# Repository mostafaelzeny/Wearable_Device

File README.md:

# AD5941 Impedance Sweep Logger 🚀

Welcome to the AD5940/AD5941 Impedance Logger project! This repository allows you to perform highly accurate impedance sweeps using an ESP32 and save the resulting data automatically to CSV files on your computer.

> [!IMPORTANT]
> The Arduino IDE's Serial Monitor cannot save files! To actually save your sweeps as CSV files, you **must** use the provided python script or shell script.

## 🛠️ How to Use

Follow these steps to run sweeps and save your data:

### 1. Upload to ESP32
Open `AD5940_Impedance.ino` in the Arduino IDE. Compile and upload the sketch to your ESP32. 
**Make sure you close the Serial Monitor in the Arduino IDE after uploading!**

### 2. Run the Logger
Open your terminal in this folder and run the provided helper script:
```bash
./save_readings.sh
```
*(Alternatively, you can run `python3 save_readings.py` directly).*

### 3. Let it Sweep!
The script will automatically connect to your board and begin saving the impedance sweeps sequentially into separate CSV files (`sweep_1.csv`, `sweep_2.csv`, `sweep_3.csv`).

> [!TIP]
> After all sweeps complete, the script will pause. Press **Enter** in your terminal to restart another round of sweeps without having to physically reset the board!

---

## ⚙️ Adjusting the Configuration

All sweep configurations are located at the very top of the `AD5940_Impedance.ino` file under **USER CONFIGURABLE PARAMETERS**. Here is a breakdown of the things you can easily change to fit your needs:

### Sweep Parameters
| Parameter | Default | Description |
|---|---|---|
| `NUM_SWEEPS` | `3` | How many full frequency sweeps to execute before pausing. |
| `SWEEP_START_FREQ` | `100.0f` | The starting frequency in Hz. |
| `SWEEP_STOP_FREQ` | `100e3f` | The stopping frequency in Hz (e.g., 100,000 Hz or 100kHz). |
| `SWEEP_POINTS` | `101` | The number of measurement data points taken per sweep. |
| `SWEEP_LOG` | `bTRUE` | Set to `bTRUE` for logarithmic frequency spacing, or `bFALSE` for linear. |

### Analog Front-End (AFE) Parameters
| Parameter | Default | Description |
|---|---|---|
| `RTIA_RESISTOR` | `HSTIARTIA_5K` | High-Speed TIA Gain. Keep this lower than your lowest expected impedance to avoid clipping. |
| `DAC_VOLT_PP` | `200.0f` | AC excitation voltage in mVpp. For biological materials, keep under 200mV. |
| `RCAL_VALUE` | `10000.0f` | Calibration resistor on the board. Make sure this matches your physical hardware (Default is 10kΩ). |

> [!CAUTION]
> If your `RTIA_RESISTOR` is too high compared to the load, the AFE will saturate and output distorted/incorrect impedance values.

---

## 🔌 Hardware Port Details

*This project is based on a port of the official AD5940 library to ESP32. It supports SPI communications at 8MHz.*

**Connections:**
The electrode switch configuration supports a **4-wire** (Kelvin) setup for high accuracy measurements. The default mapping in the code is:
- **CE0**: Drive (Force +)
- **AIN1**: Positive Sense (Sense +)
- **AIN2**: Negative Sense (Sense -)
- **AIN3**: Current Return (Force -)

*(If you are using a different 4-wire pinout, you can easily change the `SWITCH_` macros under the USER CONFIGURABLE PARAMETERS section of `AD5940_Impedance.ino`)*

*Disclaimer: This library is not officially endorsed by Analog Devices.*

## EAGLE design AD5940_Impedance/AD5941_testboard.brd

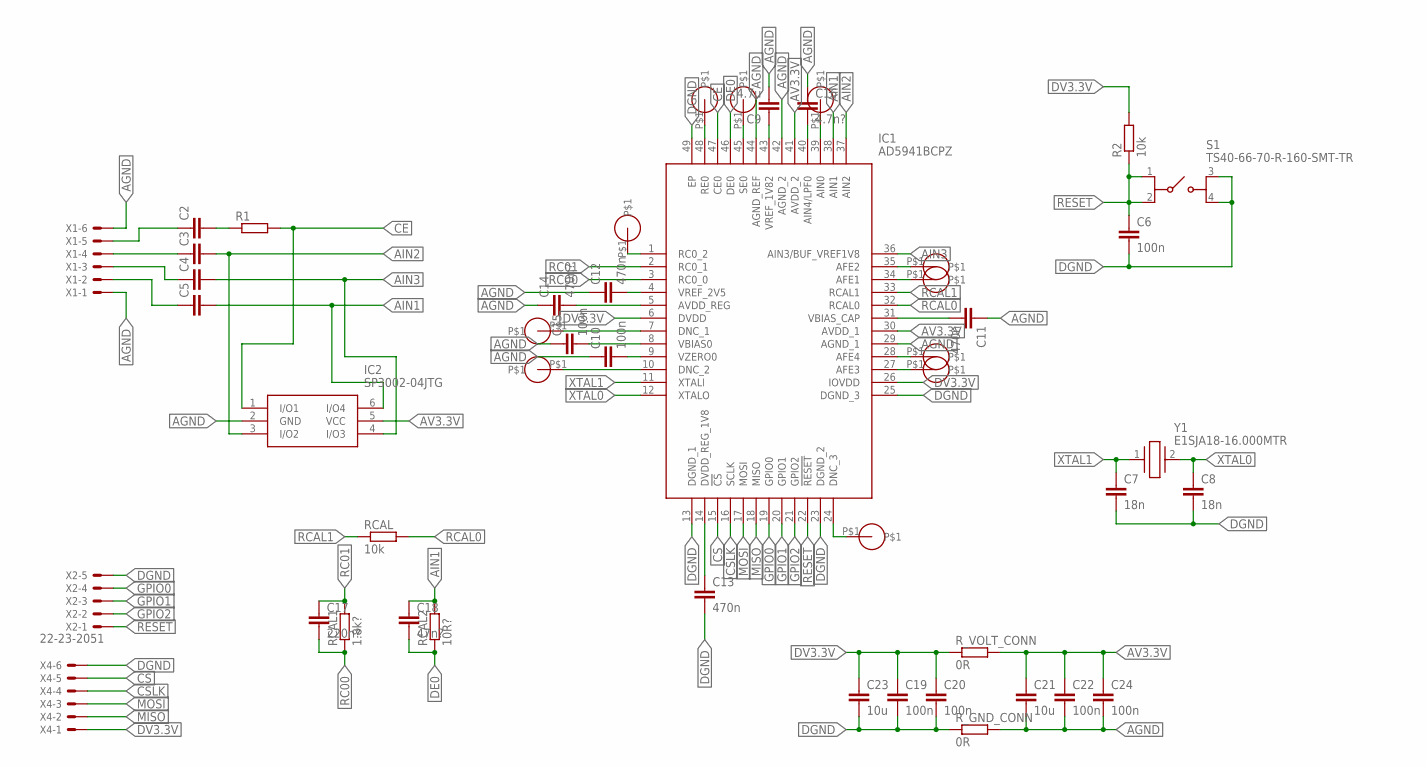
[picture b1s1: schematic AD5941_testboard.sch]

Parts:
C2, C3, C4, C5: C-EUC0805; C0805
C6, C10, C15, C19, C20, C22, C24: 100n; C0805
C7, C8: 18n; C0805
C9: 4.7u; C0805
C11, C12, C13: 470n; C0805
C14: 470n?; C0805
C16: 4.7n?; C0805
C17: 220n?; C0805
C18: 47n?; C0805
C21, C23: 10u; C0805
IC1: AD5941BCPZ; QFN50P700X700X80-49N
IC2: SP3002-04JTG; SOT65P220X110-6N
R1: R-EU_R0603; R0603
R2: 10k; R0603
RCAL: 10k; R0603
RCAL1: 1.8k?; R0603
RCAL2: 10R?; R0603
R_GND_CONN: 0R; R0603
R_VOLT_CONN: 0R; R0603
S1: TS40-66-70-R-160-SMT-TR; TS406670R160SMTTR
U$1, U$2, U$3, U$4, U$5, U$6, U$7, U$8, U$9, U$10, U$11: 1XPIN+HOLE
X1, X4: 22-23-2061
X2: 22-23-2051
Y1: E1SJA18-16.000MTR; E1SJA1816000MTR

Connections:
AGND: C9.2, C10.1, C11.1, C12.1, C14.1, C15.1, C16.1, C21.2, C22.2, C24.2, IC1.29 (AGND_1), IC1.42 (AGND_2), IC1.44 (AGND_REF), IC2.2 (GND), R_GND_CONN.2, X1.1, X1.6
AIN1: C5.2, C18.1, IC1.38 (AIN1), IC2.6 (I/O4), RCAL2.2
AIN2: C3.2, IC1.37 (AIN2), IC2.3 (I/O2)
AIN3: C4.2, IC1.36 (AIN3/BUF_VREF1V8), IC2.4 (I/O3)
AV3.3V: C21.1, C22.1, C24.1, IC1.30 (AVDD_1), IC1.41 (AVDD_2), IC2.5 (VCC), R_VOLT_CONN.2
CE: IC1.47 (CE0), IC2.1 (I/O1), R1.2
CS: IC1.15 (!CS), X4.5
CSLK: IC1.16 (SCLK), X4.4
DE0: C18.2, IC1.46 (DE0), RCAL2.1
DGND: C6.2, C7.2, C8.2, C13.2, C19.2, C20.2, C23.2, IC1.13 (DGND_1), IC1.23 (DGND_2), IC1.25 (DGND_3), IC1.49 (EP), R_GND_CONN.1, S1.3 (NO_1), S1.4 (NO_2), X2.5, X4.6
DV3.3V: C19.1, C20.1, C23.1, IC1.6 (DVDD), IC1.26 (IOVDD), R2.2, R_VOLT_CONN.1, X4.1
GPIO0: IC1.19 (GPIO0), X2.4
GPIO1: IC1.20 (GPIO1), X2.3
GPIO2: IC1.21 (GPIO2), X2.2
MISO: IC1.18 (MISO), X4.2
MOSI: IC1.17 (MOSI), X4.3
unnamed: C2.2, R1.1
unnamed: C2.1, X1.5
unnamed: C3.1, X1.4
unnamed: C4.1, X1.3
unnamed: C5.1, X1.2
unnamed: C13.1, IC1.14 (DVDD_REG_1V8)
unnamed: C12.2, IC1.4 (VREF_2V5)
unnamed: C11.2, IC1.31 (VBIAS_CAP)
unnamed: C14.2, IC1.5 (AVDD_REG)
unnamed: C9.1, IC1.43 (VREF_1V82)
unnamed: C10.2, IC1.9 (VZERO0)
unnamed: C15.2, IC1.8 (VBIAS0)
unnamed: C16.2, IC1.40 (AIN4/LPF0)
unnamed: IC1.24 (DNC_3), U$1.P$1
unnamed: IC1.27 (AFE3), U$9.P$1
unnamed: IC1.28 (AFE4), U$10.P$1
unnamed: IC1.34 (AFE1), U$8.P$1
unnamed: IC1.35 (AFE2), U$7.P$1
unnamed: IC1.10 (DNC_2), U$3.P$1
unnamed: IC1.1 (RC0_2), U$2.P$1
unnamed: IC1.7 (DNC_1), U$11.P$1
unnamed: IC1.48 (RE0), U$4.P$1
unnamed: IC1.45 (SE0), U$5.P$1
unnamed: IC1.39 (AIN0), U$6.P$1
RC00: C17.2, IC1.3 (RC0_0), RCAL1.1
RC01: C17.1, IC1.2 (RC0_1), RCAL1.2
RCAL0: IC1.32 (RCAL0), RCAL.2
RCAL1: IC1.33 (RCAL1), RCAL.1
RESET: C6.1, IC1.22 (!RESET), R2.1, S1.1 (COM_1), S1.2 (COM_2), X2.1
XTAL0: C8.1, IC1.12 (XTALO), Y1.2
XTAL1: C7.1, IC1.11 (XTALI), Y1.1

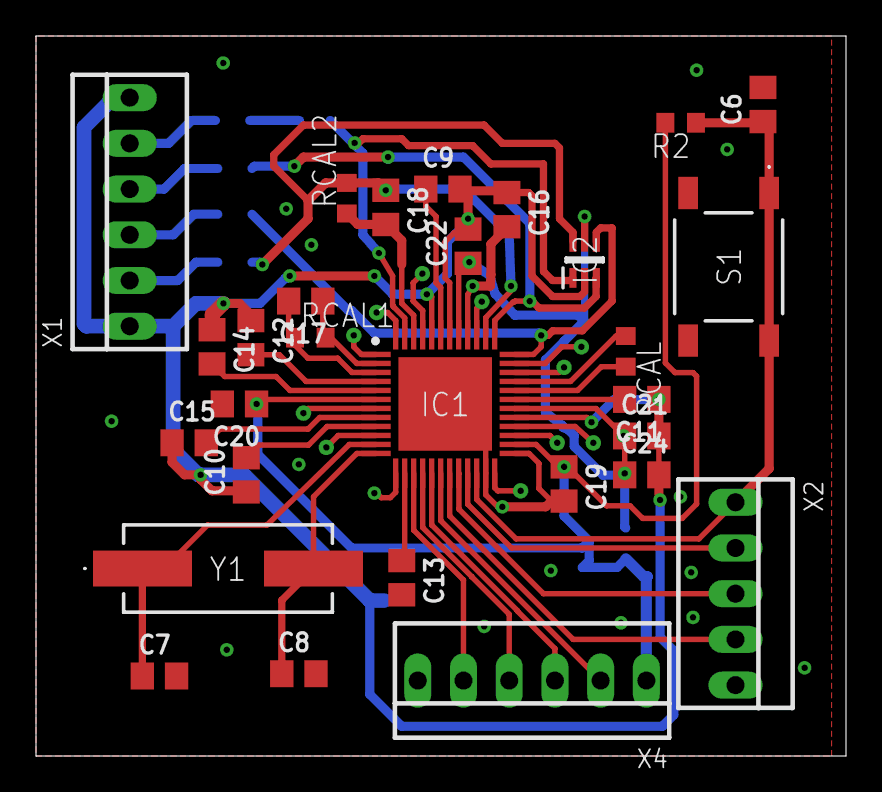
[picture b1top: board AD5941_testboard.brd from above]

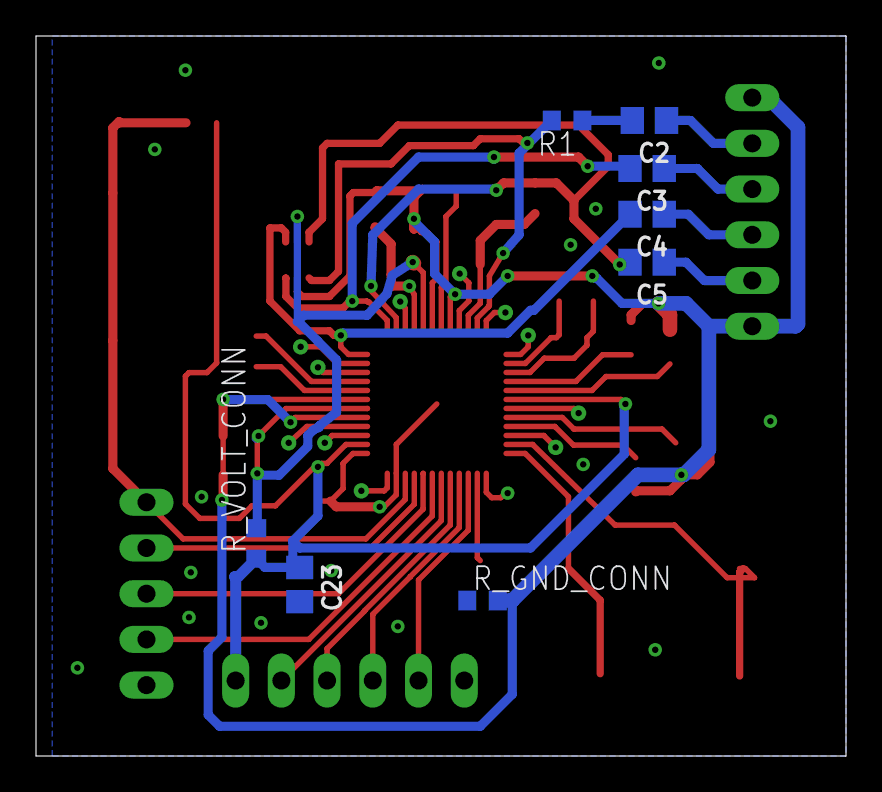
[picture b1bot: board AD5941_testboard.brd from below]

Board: 2 copper layers, 45.0 x 40.0 mm, 48 parts (8 on the bottom side), 47 nets.

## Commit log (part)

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2026-05-10 Add ESP32 AD5933 web dashboard sessions
2026-05-10 Update impedance dashboard spectroscopy charts
2026-06-07 web_connection
2026-06-27 impedance_sensor_ad5941
2026-06-27 Ignore .vscode folder
